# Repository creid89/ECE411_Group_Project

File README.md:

# ECE411_Group_Project
A repository for our PSU ECE411 Practicum Project

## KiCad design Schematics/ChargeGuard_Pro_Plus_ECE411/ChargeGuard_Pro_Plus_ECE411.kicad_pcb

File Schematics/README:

Store Schematics in this folder

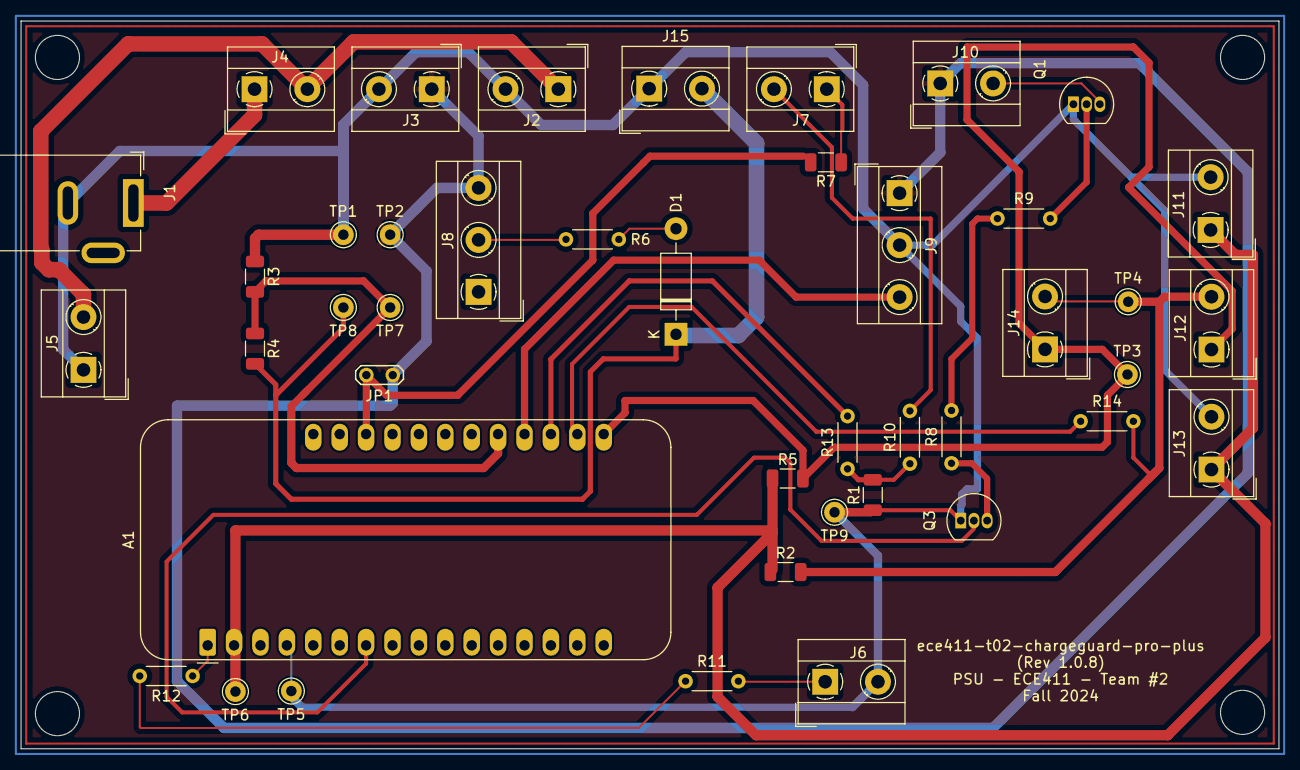
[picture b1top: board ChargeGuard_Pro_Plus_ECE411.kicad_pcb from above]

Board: 2 copper layers, 121.0 x 70.0 mm, 43 parts (0 on the bottom side), 26 nets.

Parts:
A1: Adafruit_Feather_HUZZAH32_ESP32; Adafruit_Feather
D1: 1N5819; D_DO-41_SOD81_P10.16mm_Horizontal
J1: Barrel_Jack_MountingPin; BarrelJack_GCT_DCJ200-10-A_Horizontal
J2: Buck Converter (12V); TerminalBlock_MetzConnect_Type101_RT01602HBWC_1x02_P5.08mm_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
J3: Buck Converter (5V output); TerminalBlock_MetzConnect_Type101_RT01602HBWC_1x02_P5.08mm_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
J4: Power Switch; TerminalBlock_MetzConnect_Type101_RT01602HBWC_1x02_P5.08mm_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
J5: Fan; TerminalBlock_MetzConnect_Type101_RT01602HBWC_1x02_P5.08mm_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
J6: Reset Switch; TerminalBlock_MetzConnect_Type101_RT01602HBWC_1x02_P5.08mm_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
J7: Power PB; TerminalBlock_MetzConnect_Type101_RT01602HBWC_1x02_P5.08mm_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
J8: Relay Module Logic; TerminalBlock_MetzConnect_Type055_RT01503HDWU_1x03_P5.00mm_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
J9: Relay Module Power; TerminalBlock_MetzConnect_Type055_RT01503HDWU_1x03_P5.00mm_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
J10: Solenoid; TerminalBlock_MetzConnect_Type101_RT01602HBWC_1x02_P5.08mm_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
J11: Sensor Power; TerminalBlock_MetzConnect_Type101_RT01602HBWC_1x02_P5.08mm_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
J12: Sensor I2C; TerminalBlock_MetzConnect_Type101_RT01602HBWC_1x02_P5.08mm_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
J13: OLED Power; TerminalBlock_MetzConnect_Type101_RT01602HBWC_1x02_P5.08mm_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
J14: OLED I2C; TerminalBlock_MetzConnect_Type101_RT01602HBWC_1x02_P5.08mm_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
J15: Battery; TerminalBlock_MetzConnect_Type101_RT01602HBWC_1x02_P5.08mm_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
JP1: Protection jumper; TestPoint_2Pads_Pitch2.54mm_Drill0.8mm
Q1: 2N3906; TO-92_Inline
Q3: 2N7000; TO-92_Inline
R1, R2, R5: 4.7k; R_1206_3216Metric
R3: 8.2k; R_1206_3216Metric
R4: 1k; R_1206_3216Metric
R6: 26; R_Axial_DIN0204_L3.6mm_D1.6mm_P5.08mm_Horizontal
R7: 2.7k; R_1206_3216Metric
R8, R9, R10, R11, R12, R13, R14: 0; R_Axial_DIN0204_L3.6mm_D1.6mm_P5.08mm_Horizontal
TP1: 5V(-); Pin_D1.0mm_L10.0mm
TP2: 5V(+); Pin_D1.0mm_L10.0mm
TP3: SDA; Pin_D1.0mm_L10.0mm
TP4: SCL; Pin_D1.0mm_L10.0mm
TP5: GND; Pin_D1.0mm_L10.0mm
TP6: 3.3V; Pin_D1.0mm_L10.0mm
TP7: VD; Pin_D1.0mm_L10.0mm
TP8: BAT; Pin_D1.0mm_L10.0mm
TP9: Via; Pin_D1.0mm_L10.0mm

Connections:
GND: A1.4 (GND), J1.2, J2.2, J3.2, J5.1, J6.2, J9.2, J11.2, J13.2, J15.1, Q1.1 (E), Q3.1 (S), R1.1, R3.1, TP1.1, TP5.1, TP9.1
I2C Power: A1.2 (3V3), J11.1, J13.1, R2.1, R5.1, TP6.1
unnamed: A1.19 (A6/IO14), R13.2
unnamed: A1.20 (A7/IO32), J9.3
unnamed: A1.21 (A8/IO15), R3.2, R4.1, TP7.1
unnamed: A1.7 (I34/A2), Q3.2 (G)
unnamed: A1.18 (SCL/IO22), R14.1
unnamed: A1.17 (SDA/IO23), J12.1, J14.1, R5.2, TP3.1
unnamed: A1.26 (USB), JP1.2 (B), R7.2
unnamed: A1.1 (~RESET), R12.1
unnamed: D1.2 (A), R6.1
unnamed: D1.1 (K), J15.2, R4.2, TP8.1
unnamed: J2.1, J4.2, J5.2
unnamed: J1.1, J4.1
unnamed: J6.1, R11.2
unnamed: J7.1, R7.1
unnamed: J7.2, R10.2
unnamed: J8.2, R6.2
unnamed: J10.2, Q1.3 (C)
unnamed: J12.2, J14.2, R2.2, R14.2, TP4.1
unnamed: Q1.2 (B), R9.2
unnamed: Q3.3 (D), R8.1
unnamed: R1.2, R10.1, R13.1
unnamed: R8.2, R9.1
unnamed: R11.1, R12.2
Power (Buck Converter '+'): J3.1, J8.3, J9.1, J10.1, JP1.1 (A), TP2.1

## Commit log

2024-10-12 Create README Weekly HW Folder
2024-10-12 Create README WPRs Folder
2024-11-01 Create COPYING
2024-11-03 Add files via upload
    Updated Version
2024-11-08 test commit
2024-11-08 Add files via upload
    Preliminary Schematic and most up to date Schematic of CHargue Guard Pro
2024-11-08 Add files via upload
    Breadboard Prototype
2024-11-08 Rename signal-2024-11-07-205029.jpeg to Prototype V1
2024-11-08 Rename Prototype V1 to Prototype V1.png
2024-11-09 Create Bill of Materials (BOM)
2024-11-09 Create Bill of Materials
2024-11-09 BOM_Revision_1.1
2024-11-16 Add files via upload
    ChargeGuard Pro ++ Folder with all previous and concurrent information
2024-11-16 Cleaned up debugging messages and redundant vchk
2024-11-19 Add files via upload
    Updated Version of Schematic as well as PCB Design
2024-11-20 ChargeGuard Pro + - 11/20/2024
2024-11-22 ChargeGuard Pro + - 11/21/2024
2024-11-22 BOM + Fab
2024-12-09 Add files via upload
    This revision will work with the 128*32 OLED
2024-12-12 BOM - Revision 1.2
2024-12-12 OSH Park - PCB layers/ChargeGuard Pro +
